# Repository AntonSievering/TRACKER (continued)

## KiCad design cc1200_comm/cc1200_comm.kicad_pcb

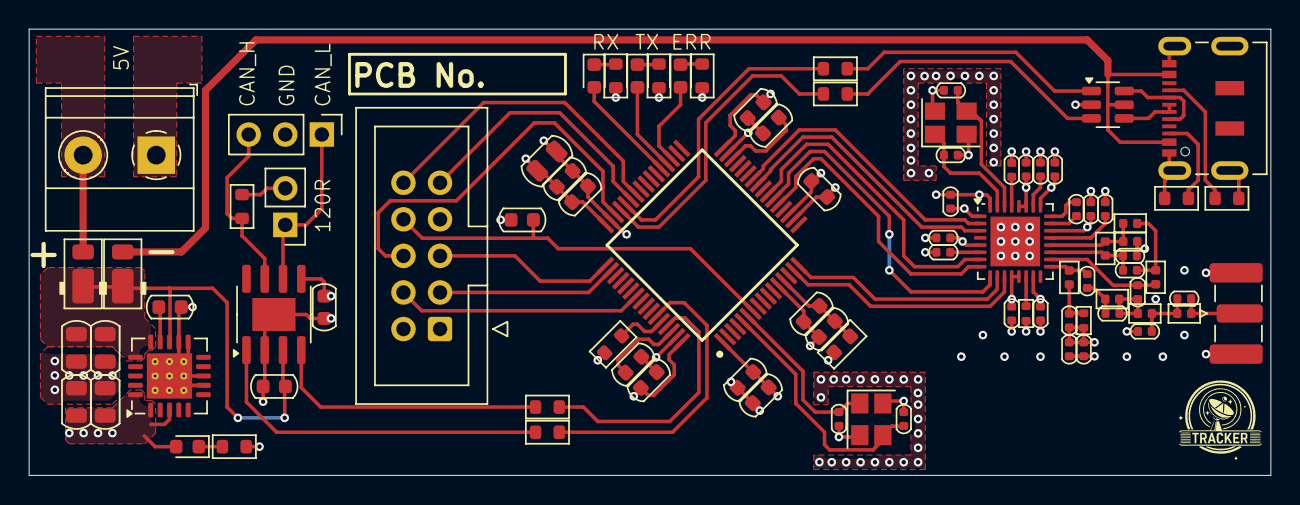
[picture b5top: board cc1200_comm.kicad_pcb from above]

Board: 4 copper layers, 86.2 x 31.0 mm, 88 parts (0 on the bottom side), 67 nets.

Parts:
C1, C2, C43, C44: 10p; C_0402_1005Metric
C3, C4, C5, C6, C7, C8, C9, C16, C19: 47n; C_0402_1005Metric
C10: 220n; C_0402_1005Metric
C11: 1.8n; C_0402_1005Metric
C12: 39p; C_0402_1005Metric
C13, C23: 10n; C_0402_1005Metric
C14, C15, C18: 5.1p; C_0402_1005Metric
C17: 2.2p; C_0402_1005Metric
C20: 6.2p; C_0402_1005Metric
C21: Tuning; C_0402_1005Metric
C22: 56p; C_0402_1005Metric
C24: 100p; C_0402_1005Metric
C25, C26, C33: 10u; C_0805_2012Metric
C27, C34, C41, C42: 1u; C_0603_1608Metric
C28, C29: 47u; C_0805_2012Metric
C30, C35, C36, C37, C38, C39, C40, C45, C46: 100n; C_0603_1608Metric
C31, C32: 2u2; C_0603_1608Metric
D1, D2: DFLS130; D_PowerDI-123
D3, D4, D5, D6: LED; D_0603_1608Metric
FB1: 1k@100MHz; L_0603_1608Metric
IC1: STM32H562RGT6; QFP50P1200X1200X160-64N
J2: Conn_02x05_Counter_Clockwise; IDC-Header_2x05_P2.54mm_Vertical
J3: Conn_Coaxial; SMA_Samtec_SMA-J-P-H-ST-EM1_EdgeMount
J4: Screw_Terminal_01x02; TerminalBlock_Phoenix_MKDS-1,5-2-5.08_1x02_P5.08mm_Horizont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
J5: USB_C_Receptacle_USB2.0; USB_C_Receptacle_JAE_DX07S016JA1R1500
J6: Conn_01x02_Pin; PinHeader_1x02_P2.54mm_Vertical
J7: Conn_01x03_Pin; PinHeader_1x03_P2.54mm_Vertical
L1, L6: 56n; L_0402_1005Metric
L2, L3: 27n; L_0402_1005Metric
L4, L5: 15n; L_0402_1005Metric
L7: 43n; L_0402_1005Metric
L8: 22n; L_0402_1005Metric
R1: 56k; R_0402_1005Metric
R2: 10; R_0402_1005Metric
R3, R7, R8, R11, R12: 0; R_0603_1608Metric
R4, R5, R6, R10: 10k; R_0603_1608Metric
R9: 120; R_0603_1608Metric
R15, R16: 5k6; R_0603_1608Metric
U1: CC1200; QFN-32-1EP_5x5mm_P0.5mm_EP3.45x3.45mm
U2: TPS7A4701xRGW; Texas_RGW0020A_VQFN-20-1EP_5x5mm_P0.65mm_EP3.15x3.15mm_Ther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
U3: MCP2542FDxMF; SOIC-8-1EP_3.9x4.9mm_P1.27mm_EP2.29x3mm
U15: USBLC6-2SC6; SOT-23-6
X1, X2: 40MHz; Crystal_SMD_Abracon_ABM8AIG-4Pin_3.2x2.5mm

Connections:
+3.3V: C3.1, C4.1, C5.1, C6.1, C7.1, C8.1, C9.1, C22.2, C23.1, C24.1, C28.1, C29.1, C33.1, C34.1, C35.1, C36.1, C37.1, C38.1, C39.1, C41.1, C45.1, D6.2 (A), FB1.2, IC1.1 (VBAT), IC1.19 (VDD_1), IC1.32 (VDD_2), IC1.48 (VDD_3), IC1.64 (VDD_4), J2.1, R2.2, U1.1 (VDD_GUARD), U1.5 (DVDD), U1.12 (DVDD), U1.13 (AVDD_IF), U1.15 (AVDD_RF), U1.22 (AVDD_SYNTH1), U1.25 (AVDD_PFD_CHP), U1.27 (AVDD_SYNTH2), U1.28 (AVDD_XOSC), U2.1 (OUT), U2.3 (SENSE/FB), U2.20 (OUT), U3.5 (VIO)
+5V: C25.1, C26.1, C46.1, D1.1 (K), D2.1 (K), U2.13 (EN), U2.15 (IN), U2.16 (IN), U3.3 (VDD)
/3V3 LDO/screw_vin: D2.2 (A), J4.2
/CC1200/ANT: C21.2, J3.1 (In), L8.2
/CC1200/GPIO0: IC1.16 (PA2), U1.10 (GPIO0)
/CC1200/GPIO3: IC1.25 (PC5), U1.3 (GPIO3)
/CC1200/cs_radio: IC1.15 (PA1), U1.11 (~CS)
/CC1200/miso: IC1.22 (PA6), U1.9 (SO(GPIO1))
/CC1200/mosi: IC1.23 (PA7), U1.7 (SI)
/CC1200/rf_lnan: L1.2, L2.1, L3.1, U1.20 (LNA_N)
/CC1200/rf_lnap: C14.1, C15.1, L1.1, U1.19 (LNA_P)
/CC1200/rf_lpf0: C11.1, U1.23 (LPF0)
/CC1200/rf_lpf1: C11.2, U1.24 (LPF1)
/CC1200/rf_net_c174: C12.2, C17.1, L4.1
/CC1200/rf_net_l171: C22.1, L6.2, R2.1
/CC1200/rf_net_l172: C17.2, C18.2, L4.2, L7.1
/CC1200/rf_net_l173: C20.2, C21.1, L7.2, L8.1
/CC1200/rf_net_l201: C15.2, L3.2, L5.1
/CC1200/rf_pa: C12.1, L6.1, U1.17 (PA)
/CC1200/rf_trxsw: C18.1, L5.2, U1.18 (TRX_SW)
/CC1200/sck: IC1.21 (PA5), U1.8 (SCLK)
/CC1200/~reset: IC1.26 (PB0), U1.2 (~RESET)
/FDCAN Tranceiver/CAN_H: J7.3, R9.2, U3.7 (CANH)
/FDCAN Tranceiver/CAN_L: J6.1, J7.1, U3.6 (CANL)
/FDCAN Tranceiver/CAN_RX: R7.2, U3.4 (RXD)
/FDCAN Tranceiver/CAN_TX: R8.2, U3.1 (TXD)
/FDCAN_RX: IC1.61 (PB8), R7.1
/FDCAN_TX: IC1.59 (PB7), R8.1
/Microcontroller/DEBUG_RX: IC1.43 (PA10), J2.9
/Microcontroller/DEBUG_TX: IC1.42 (PA9), J2.10
/Microcontroller/JTCK: IC1.49 (PA14), J2.5
/Microcontroller/JTDI: IC1.50 (PA15), J2.3
/Microcontroller/JTDO: IC1.55 (PB3), J2.4
/Microcontroller/JTMS: IC1.46 (PA13), J2.6
/Microcontroller/NRST: C30.1, IC1.7 (NRST), J2.8
/Microcontroller/OSC_IN: C43.2, IC1.5 (PH0-OSC_IN), X2.3
/Microcontroller/OSC_OUT: C44.2, IC1.6 (PH1-OSC_OUT), X2.1
/Microcontroller/PA11: IC1.44 (PA11), R12.2
/Microcontroller/PA12: IC1.45 (PA12), R11.2
/Microcontroller/PB14: D4.2 (A), IC1.35 (PB14)
/Microcontroller/PB15: D3.2 (A), IC1.36 (PB15)
/Microcontroller/PC6: D5.2 (A), IC1.37 (PC6)
/Microcontroller/boot0_r: IC1.60 (BOOT0), R3.2
/Microcontroller/stm32_vdda: C40.1, C42.1, FB1.1, IC1.13 (VDDA)
/Microcontroller/stm_vcap1: C31.1, IC1.30 (VCAP_1)
/Microcontroller/stm_vcap2: C32.1, IC1.62 (VCAP_2)
/USB Device/usb_cc: J5.A5 (CC1), R16.1
/USB Device/usb_vbus: D1.2 (A), J5.A4 (VBUS), J5.A9 (VBUS), J5.B4 (VBUS), J5.B9 (VBUS), U15.5 (VBUS)
/USB Device/usb_vconn: J5.B5 (CC2), R15.1
/USB Device/usbd+: R11.1, U15.3 (I/O2)
/USB Device/usbd-: R12.1, U15.1 (I/O1)
/USB Device/usbdm_in: J5.A7 (D-), J5.B7 (D-), U15.6 (I/O1)
/USB Device/usbdp_in: J5.A6 (D+), J5.B6 (D+), U15.4 (I/O2)
GND: C1.1, C2.1, C3.2, C4.2, C5.2, C6.2, C7.2, C8.2, C9.2, C10.2, C13.2, C14.2, C16.2, C19.2, C20.1, C23.2, C24.2, C25.2, C26.2, C27.2, C28.2, C29.2, C30.2, C31.2, C32.2, C33.2, C34.2, C35.2, C36.2, C37.2, C38.2, C39.2, C40.2, C41.2, C42.2, C43.1, C44.1, C45.2, C46.2, IC1.12 (VSSA), IC1.18 (VSS_1), IC1.31 (VSS_2), IC1.47 (VSS_3), IC1.63 (VSS_4), J2.2, J2.7, J3.2 (Ext), J4.1, J5.A1 (GND), J5.A12 (GND), J5.B1 (GND), J5.B12 (GND), J5.S1 (SHIELD), J7.2, L2.2, R1.2, R3.1, R4.1, R5.1, R6.1, R10.1, R15.2, R16.2, U1.32 (EXT_XOSC), U1.33 (GND_EP), U2.7 (GND), U2.8 (1.6V), U2.11 (0.2V), U2.12 (0.1V), U2.21 (EP), U3.2 (VSS), U3.9 (VSS), U15.2 (GND), X1.2, X1.4, X2.2, X2.4
unnamed: D3.1 (K), R5.2
unnamed: D4.1 (K), R4.2
unnamed: D5.1 (K), R6.2
unnamed: D6.1 (K), R10.2
unnamed: J6.2, R9.1
unnamed: C10.1, U1.6 (DCPL)
unnamed: C16.1, U1.26 (DCPL_PFD_CHP)
unnamed: C13.1, U1.21 (DCPL_VCO)
unnamed: C19.1, U1.29 (DCPL_XOSC)
unnamed: R1.1, U1.14 (RBIAS)
unnamed: C1.2, U1.30 (XOSC_Q1), X1.3
unnamed: C2.2, U1.31 (XOSC_Q2), X1.1
unnamed: C27.1, U2.14 (NR)

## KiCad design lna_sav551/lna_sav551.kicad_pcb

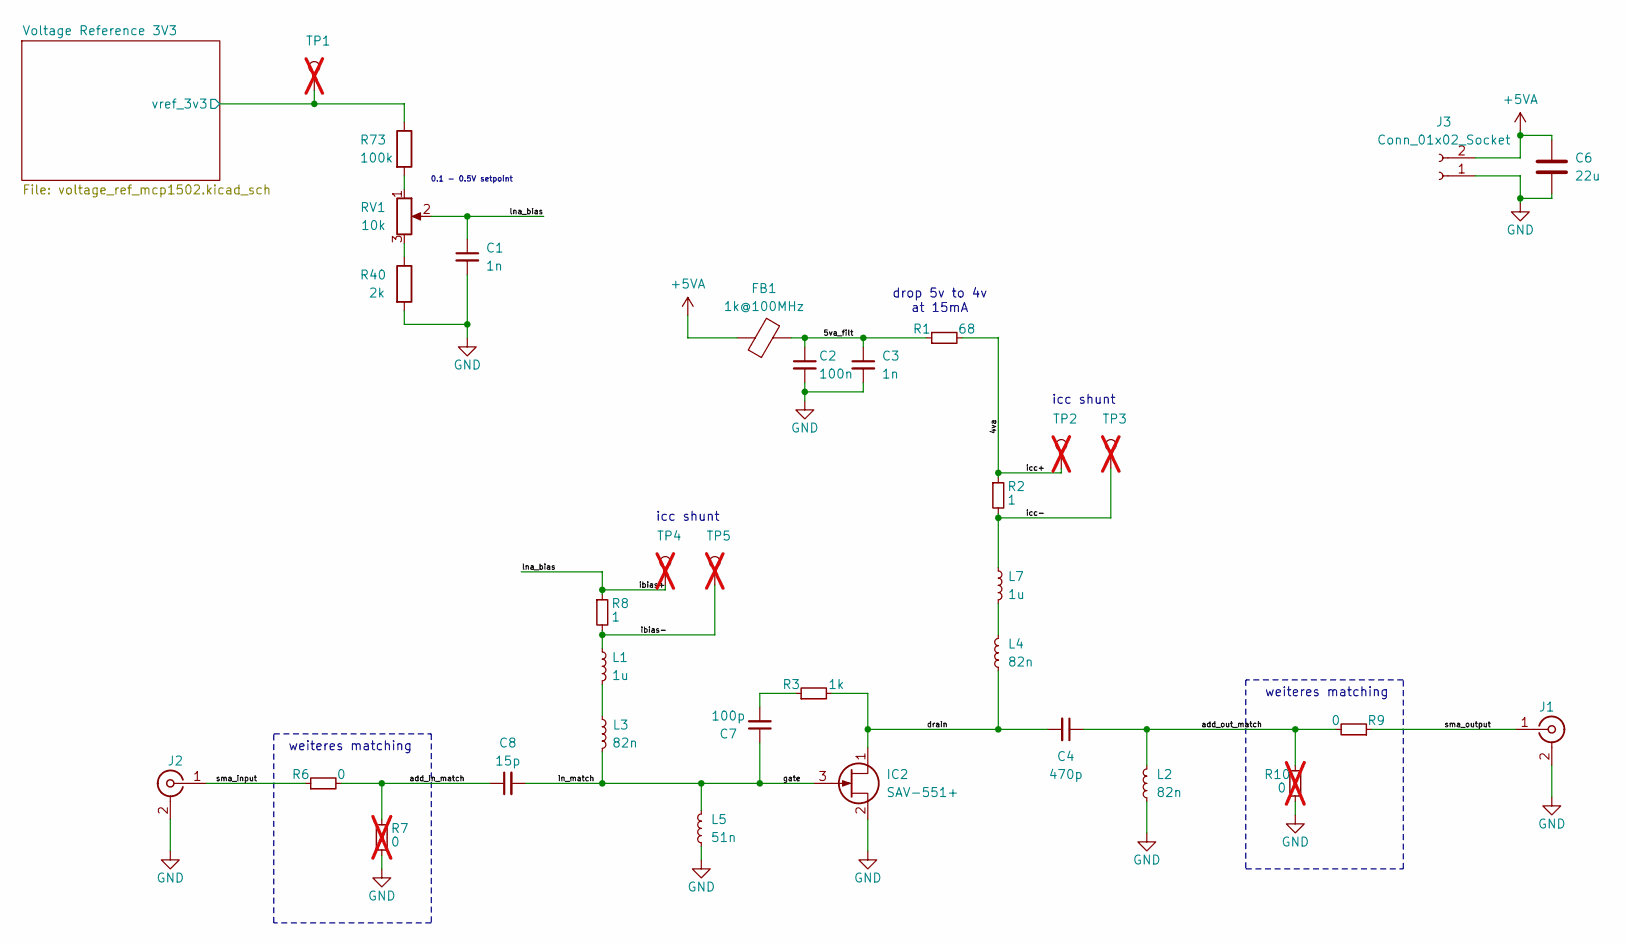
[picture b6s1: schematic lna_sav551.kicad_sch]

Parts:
C1, C3: 1n; R_0603_1608Metric
C2: 100n; R_0603_1608Metric
C4: 470p; R_0603_1608Metric; MPN C0603C471F8HACTU
C6: 22u; R_0805_2012Metric
C7: 100p; R_0603_1608Metric
C8: 15p; R_0603_1608Metric; MPN C0603C150J8HACTU
FB1: 1k@100MHz; R_0603_1608Metric; MPN 81-BLM18KG102SH1D
IC2: SAV-551+; SAV551; Manufacturer_Part_Number SAV-551+
J1, J2: SMA; SMA_Edge_Mount
J3: Conn_01x02_Socket; PinHeader_1x02_P2.54mm_Vertical
L1, L7: 1u; L_0805_2012Metric; MPN MCL2012V1-1R0-R
L2, L3, L4: 82n; R_0603_1608Metric; MPN AIMC-0603-82NJ-T
L5: 51n; R_0603_1608Metric; MPN LQW18AN51NG00D
R1: 68; R_0603_1608Metric
R2, R8: 1; R_0603_1608Metric
R3: 1k; R_0603_1608Metric
R6, R9: 0; R_0603_1608Metric
R7, R10: 0; R_0603_1608Metric; not fitted
R40: 2k; R_0603_1608Metric
R73: 100k; R_0603_1608Metric
RV1: 10k; Potentiometer_Bourns_3386X_Horizontal; MPN PTN10-C10HB20
TP1, TP2, TP3, TP4, TP5: TestPoint; TestPoint_Pad_D1.0mm; not fitted

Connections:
+5VA: C6.1, FB1.1, J3.2; also elsewhere on the board
/4va: R1.2, R2.1, TP2.1
/5va_filt: C2.1, C3.1, FB1.2, R1.1
/Voltage Reference 3V3/vref_3v3: R73.1, TP1.1; also elsewhere on the board
/add_in_match: C8.1, R6.2, R7.1
/add_out_match: C4.1, L2.2, R9.2, R10.1
/drain: C4.2, IC2.1, L4.1, R3.2
/gate: C7.1, C8.2, IC2.3, L3.1, L5.2
/ibias+: C1.1, R8.1, RV1.2, TP4.1
/ibias-: L1.1, R8.2, TP5.1
/icc-: L7.1, R2.2, TP3.1
/sma_input: J2.1 (In), R6.1
/sma_output: J1.1 (In), R9.1
GND: C1.2, C2.2, C3.2, C6.2, IC2.2, IC2.4 (GND), J1.2 (Ext), J2.2 (Ext), J3.1, L2.1, L5.1, R7.2, R10.2, R40.2; also elsewhere on the board
unnamed: C7.2, R3.1
unnamed: L1.2, L3.2
unnamed: L4.2, L7.2
unnamed: R40.1, RV1.3
unnamed: R73.2, RV1.1

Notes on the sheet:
weiteres matching
drop 5v to 4v at 15mA
0.1 - 0.5V setpoint
icc shunt

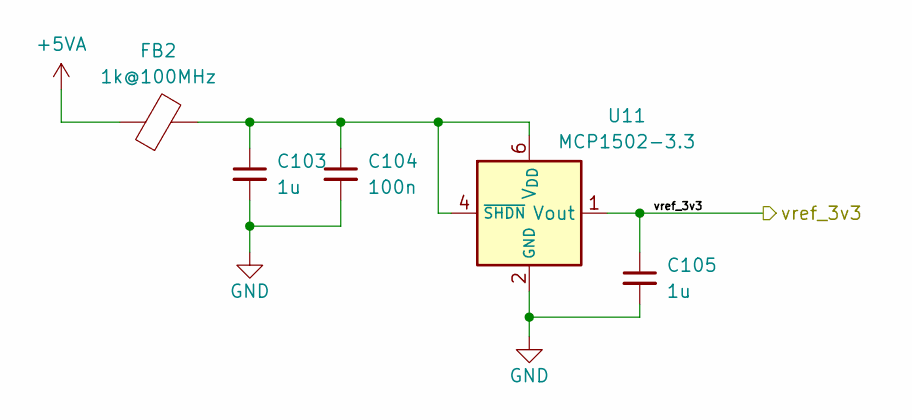
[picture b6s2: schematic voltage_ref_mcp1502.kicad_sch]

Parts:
C103, C105: 1u; R_0603_1608Metric
C104: 100n; R_0603_1608Metric
FB2: 1k@100MHz; R_0603_1608Metric; MPN 81-BLM18KG102SH1D
U11: MCP1502-3.3; TSOT-23-6; MPN 579-MCP1502T-33E/CHY

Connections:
+5VA: FB2.1; also elsewhere on the board
/Voltage Reference 3V3/vref_3v3: C105.1, U11.1 (Vout); also elsewhere on the board
GND: C103.2, C104.2, C105.2, U11.2 (GND), U11.3 (GND), U11.5 (GND); also elsewhere on the board
unnamed: C103.1, C104.1, FB2.2, U11.4 (~SHDN), U11.6 (V_{DD})

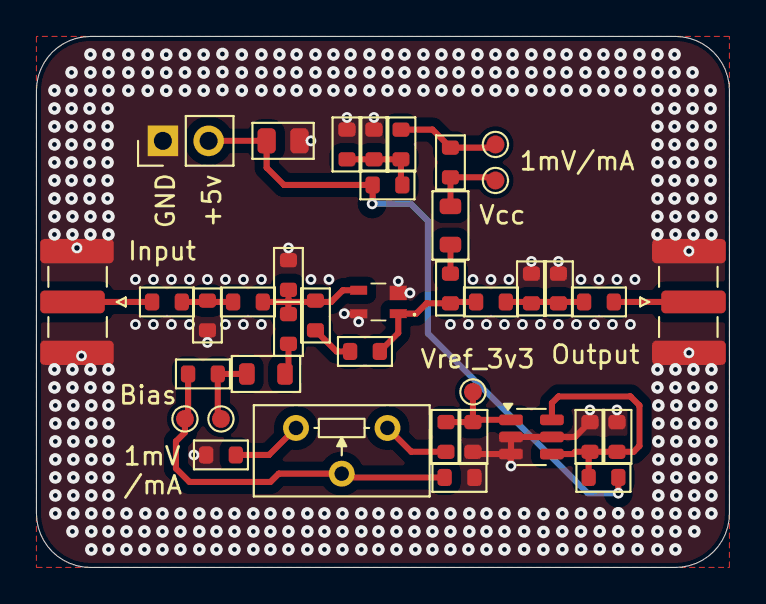
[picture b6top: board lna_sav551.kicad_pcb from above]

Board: 4 copper layers, 38.5 x 29.5 mm, 39 parts (0 on the bottom side), 20 nets.

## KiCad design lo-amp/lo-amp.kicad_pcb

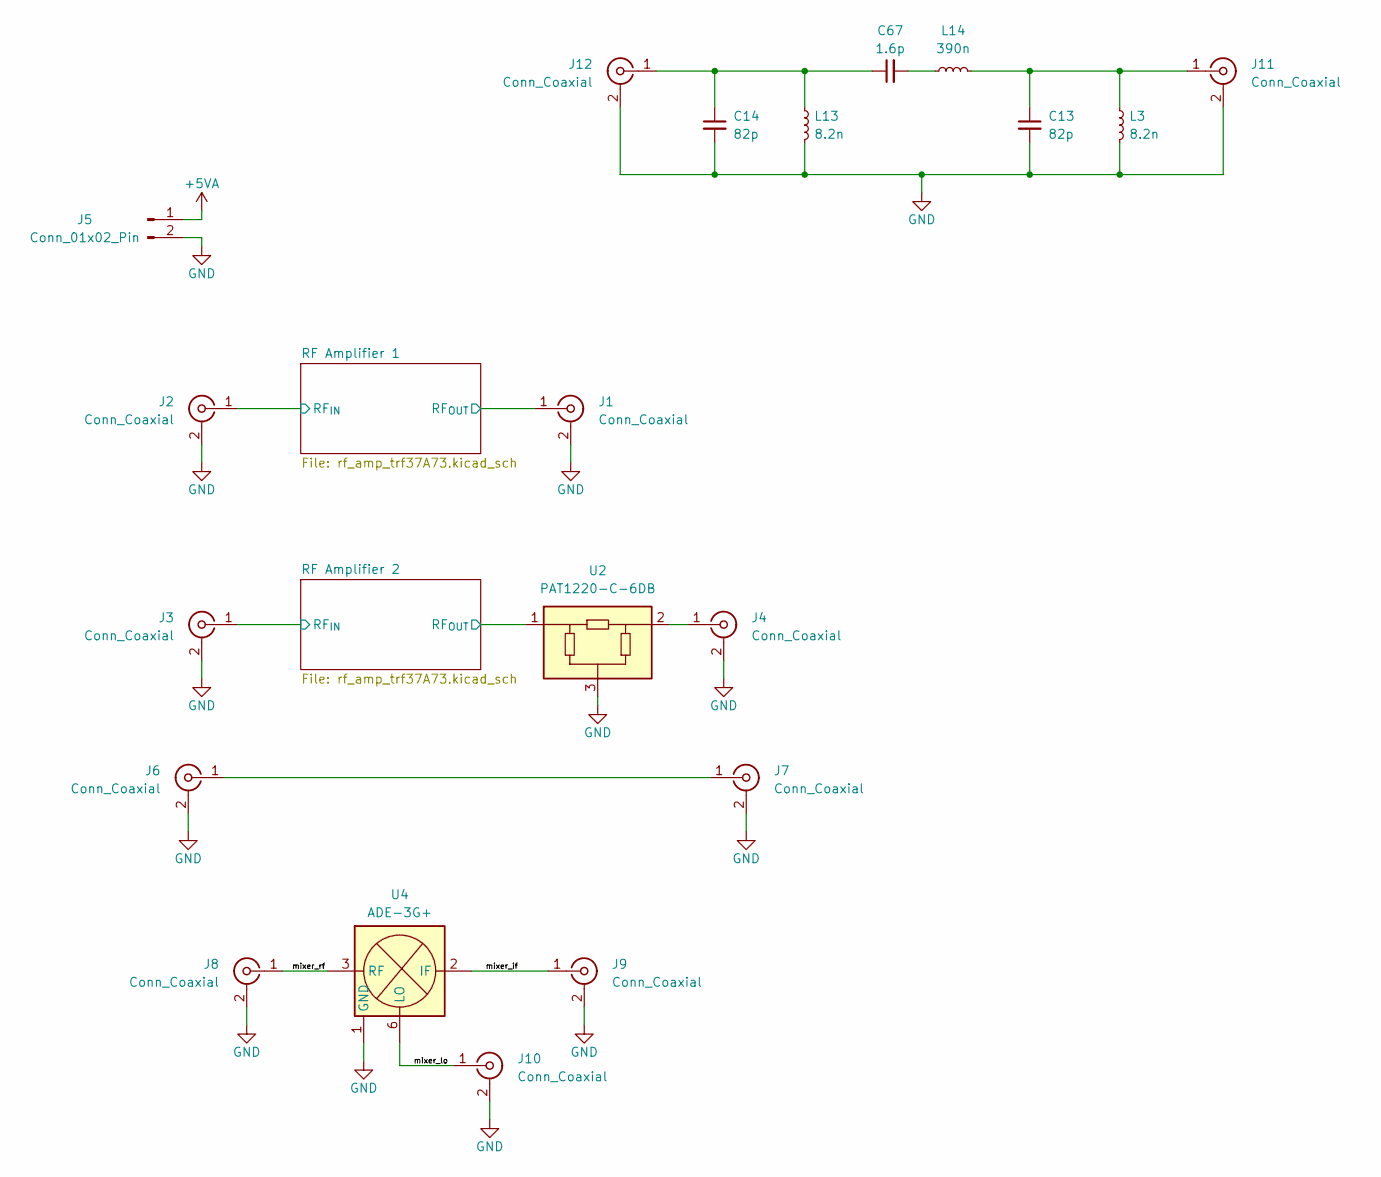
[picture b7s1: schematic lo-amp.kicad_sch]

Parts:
C13, C14: 82p; C_0603_1608Metric; MPN CC0603GRNPO9BN820
C67: 1.6p; C_0603_1608Metric; MPN RF18N1R6B500CT
J1, J2, J3, J4, J6, J7, J8, J9, J10, J11, J12: Conn_Coaxial; SMA_Edge_Mount
J5: Conn_01x02_Pin; PinHeader_1x02_P2.54mm_Vertical
L3, L13: 8.2n; L_0603_1608Metric; MPN 7447860082G
L14: 390n; L_0603_1608Metric; MPN 7447860239G
U2: PAT1220-C-6DB; RF_Attenuator_Susumu_PAT1220; MPN PAT1220-C-6DB-T5
U4: ADE-3G+; Mini-Circuits_CD542_LandPatternPL-052; MPN 139-ADE-3G

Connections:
+5VA: J5.1; also elsewhere on the board
/RF Amplifier 1/RF_{IN}: J2.1 (In); also elsewhere on the board
/RF Amplifier 1/RF_{OUT}: J1.1 (In); also elsewhere on the board
/RF Amplifier 2/RF_{IN}: J3.1 (In); also elsewhere on the board
/RF Amplifier 2/RF_{OUT}: U2.1; also elsewhere on the board
/mixer_if: J9.1 (In), U4.2 (IF)
/mixer_lo: J10.1 (In), U4.6 (LO)
/mixer_rf: J8.1 (In), U4.3 (RF)
GND: C13.2, C14.2, J1.2 (Ext), J2.2 (Ext), J3.2 (Ext), J4.2 (Ext), J5.2, J6.2 (Ext), J7.2 (Ext), J8.2 (Ext), J9.2 (Ext), J10.2 (Ext), J11.2 (Ext), J12.2 (Ext), L3.2, L13.2, U2.3, U4.1 (GND), U4.4 (GND), U4.5 (GND); also elsewhere on the board
unnamed: C67.2, L14.1
unnamed: J4.1 (In), U2.2
unnamed: J6.1 (In), J7.1 (In)
unnamed: C13.1, J11.1 (In), L3.1, L14.2
unnamed: C14.1, C67.1, J12.1 (In), L13.1

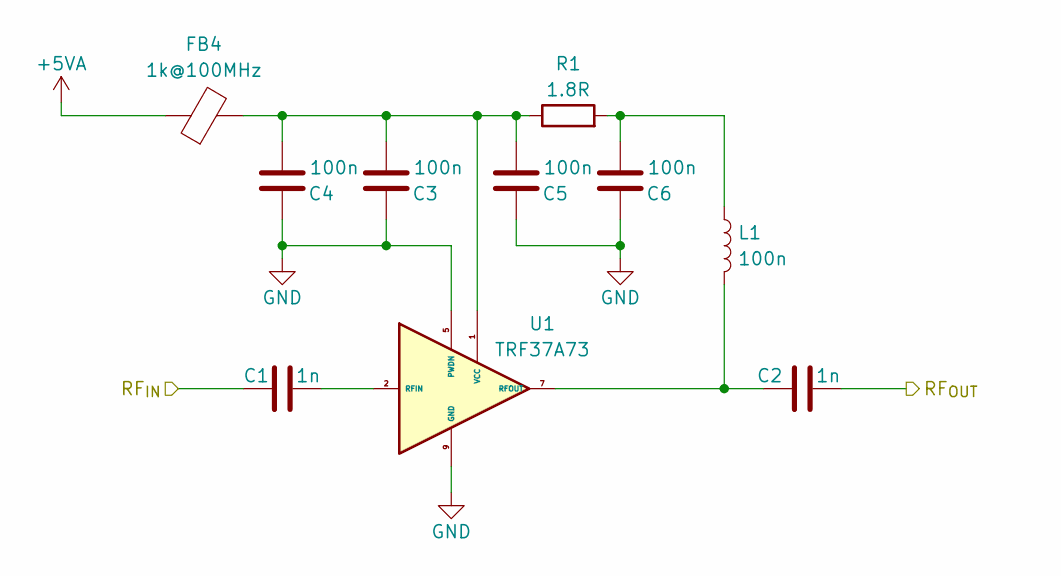
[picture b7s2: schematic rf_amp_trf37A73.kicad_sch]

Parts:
C1, C2: 1n; C_0402_1005Metric; MPN CL05B102KB5NNNC
C3, C4, C5, C6: 100n; C_0603_1608Metric
FB4: 1k@100MHz; L_0603_1608Metric; MPN 81-BLM18KG102SH1D
L1: 100n; L_0603_1608Metric; MPN MLZ1608DR10DT000
R1: 1.8R; R_0603_1608Metric; MPN CRCW06031R80JNEA
U1: TRF37A73; WSON-8-1EP_2x2mm_P0.5mm_EP0.9x1.6mm; MPN TRF37A73

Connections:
+5VA: FB4.1; also elsewhere on the board
/RF Amplifier 1/RF_{IN}: C1.1; also elsewhere on the board
/RF Amplifier 1/RF_{OUT}: C2.2; also elsewhere on the board
GND: C3.1, C4.1, C5.1, C6.1, U1.3 (NC), U1.4 (NC), U1.5 (PWDN), U1.6 (NC), U1.8 (NC), U1.9 (GND); also elsewhere on the board
unnamed: C6.2, L1.1, R1.2
unnamed: C1.2, U1.2 (RFIN)
unnamed: C2.1, L1.2, U1.7 (RFOUT)
unnamed: C3.2, C4.2, C5.2, FB4.2, R1.1, U1.1 (VCC)

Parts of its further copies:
C7, C9, C10, C11: 100n; C_0603_1608Metric
C8, C12: 1n; C_0402_1005Metric; MPN CL05B102KB5NNNC
FB1: 1k@100MHz; L_0603_1608Metric; MPN 81-BLM18KG102SH1D
L2: 100n; L_0603_1608Metric; MPN MLZ1608DR10DT000
R2: 1.8R; R_0603_1608Metric; MPN CRCW06031R80JNEA
U3: TRF37A73; WSON-8-1EP_2x2mm_P0.5mm_EP0.9x1.6mm; MPN TRF37A73

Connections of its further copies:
+5VA: FB1.1; also elsewhere on the board
/RF Amplifier 2/RF_{IN}: C8.1; also elsewhere on the board
/RF Amplifier 2/RF_{OUT}: C12.2; also elsewhere on the board
GND: C7.1, C9.1, C10.1, C11.1, U3.3 (NC), U3.4 (NC), U3.5 (PWDN), U3.6 (NC), U3.8 (NC), U3.9 (GND); also elsewhere on the board
unnamed: C11.2, L2.1, R2.2
unnamed: C8.2, U3.2 (RFIN)
unnamed: C12.1, L2.2, U3.7 (RFOUT)
unnamed: C7.2, C9.2, C10.2, FB1.2, R2.1, U3.1 (VCC)

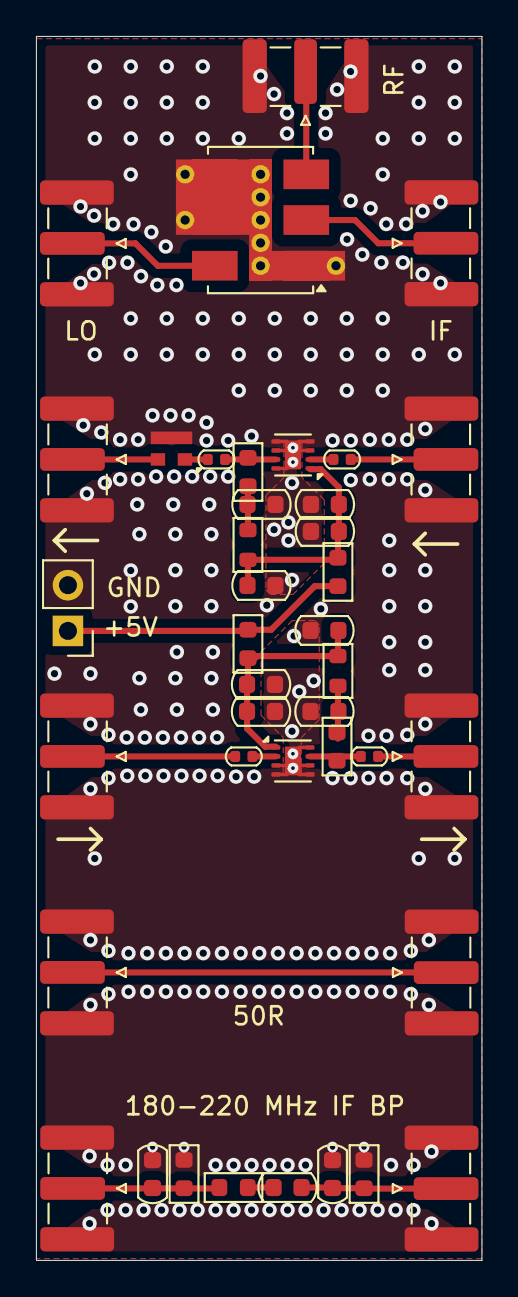
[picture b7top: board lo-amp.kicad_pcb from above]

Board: 4 copper layers, 24.8 x 68.0 mm, 40 parts (0 on the bottom side), 22 nets.
